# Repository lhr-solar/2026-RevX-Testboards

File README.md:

# RevX
https://www.notion.so/lhrs/Summer-2026-Rev-X-Experimental-Boards-3506309905da81d8914cc86e8693fb08?source=copy_link

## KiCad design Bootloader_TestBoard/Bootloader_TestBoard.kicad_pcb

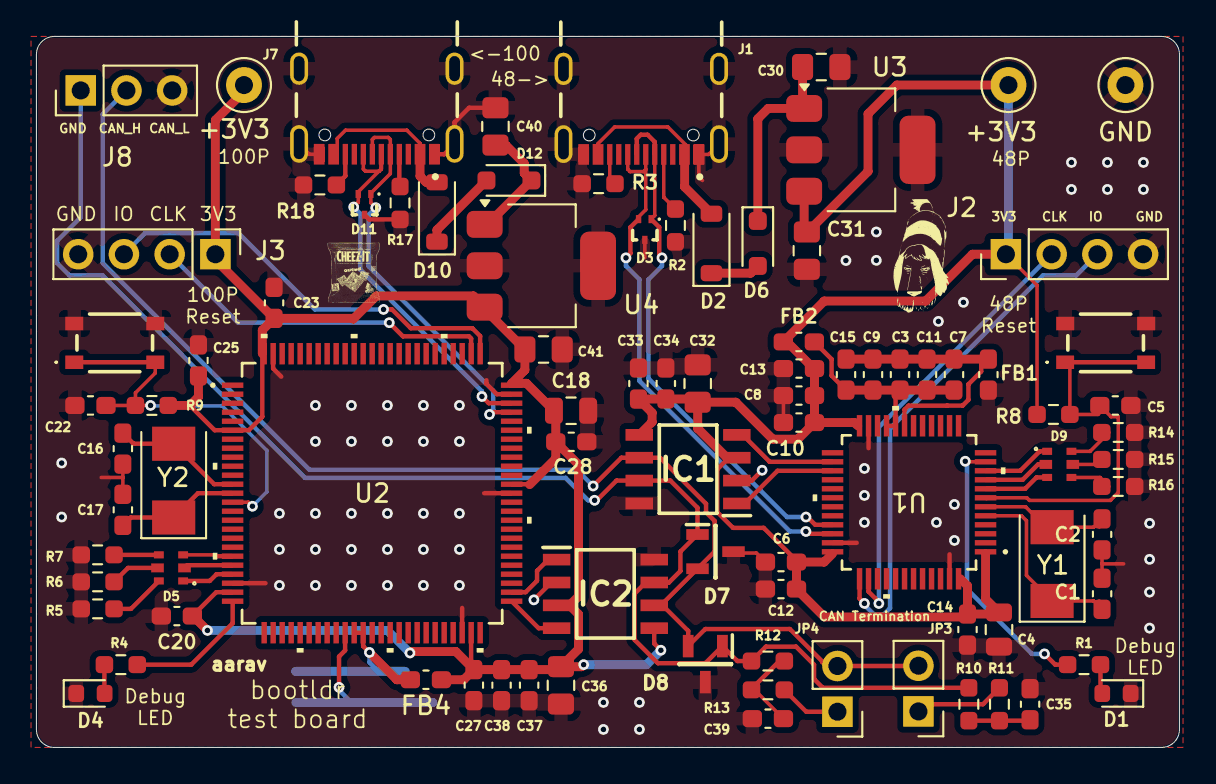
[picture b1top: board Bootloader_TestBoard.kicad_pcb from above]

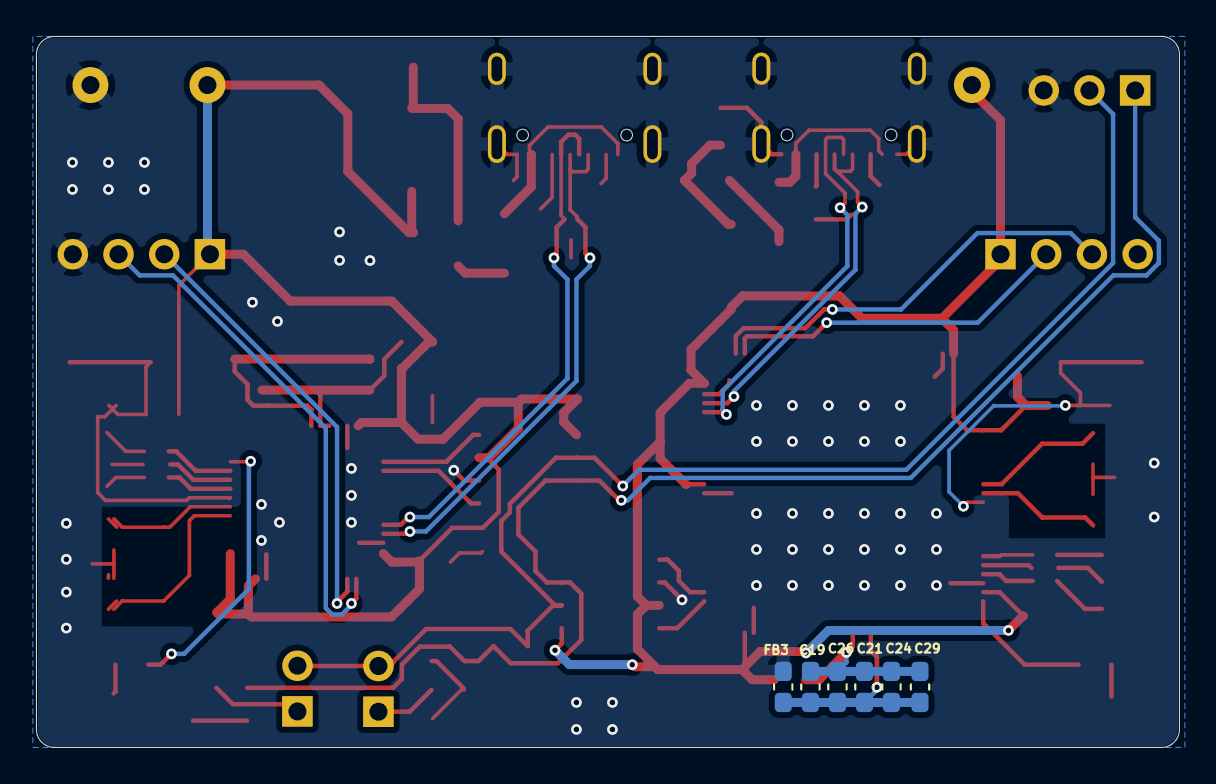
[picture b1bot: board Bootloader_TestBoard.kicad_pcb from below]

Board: 2 copper layers, 63.5 x 39.5 mm, 95 parts (6 on the bottom side), 57 nets.

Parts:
+3V3, +3V3#2: 3.3V; TestPoint_Loop_D1.80mm_Drill1.0mm_Beaded
C1, C2, C16, C17: 26p; C_0603_1608Metric_Pad1.08x0.95mm_HandSolder
C3, C5, C6, C7, C8, C10, C12, C13, C14: 0.1uF; C_0603_1608Metric_Pad1.08x0.95mm_HandSolder
C4: 10uF; C_0805_2012Metric
C9, C11: 1uF; C_0603_1608Metric_Pad1.08x0.95mm_HandSolder
C15: 100nF; C_0603_1608Metric_Pad1.08x0.95mm_HandSolder
C18: 10u; C_0805_2012Metric
C19, C20, C21, C22, C23, C25, C27, C28, C29, C33, C34, C35, C37, C38, C39: 0.1u; C_0603_1608Metric_Pad1.08x0.95mm_HandSolder
C24, C26: 1u; C_0603_1608Metric_Pad1.08x0.95mm_HandSolder
C30, C31, C32, C36, C40, C41: 10u; C_0805_2012Metric_Pad1.18x1.45mm_HandSolder
D1, D4: LED; LED_0603_1608Metric
D2, D10: D; D_SOD-123
D3, D11: TPD2EUSB30DRTR; USB_TVS
D5, D9: RGB_LED
D6, D12: SBA130CH-AU_R1_000A1; D_SOD-323_HandSoldering
D7, D8: CDSOT23-T24CAN
FB1, FB2, FB3, FB4: FerriteBead; C_0603_1608Metric_Pad1.08x0.95mm_HandSolder
GND: TestPoint; TestPoint_Loop_D1.80mm_Drill1.0mm_Beaded
IC1, IC2: TCAN3413DR
J1, J7: USB_C_Receptacle; USB_Conn
J2, J3: SWD; PinHeader_1x04_P2.54mm_Vertical
J8: Conn_01x03; PinHeader_1x03_P2.54mm_Vertical
JP3, JP4: TRM; PinHeader_1x02_P2.54mm_Vertical
R1, R4, R5, R6, R7, R14, R15, R16: 1k; R_0603_1608Metric_Pad0.98x0.95mm_HandSolder
R2, R3, R17, R18: 5.1k; R_0603_1608Metric_Pad0.98x0.95mm_HandSolder
R8, R9: 10k; R_0603_1608Metric_Pad0.98x0.95mm_HandSolder
R10, R11, R12, R13: 60; R_0603_1608Metric_Pad0.98x0.95mm_HandSolder
Reset1: Reset; TL3365AF180QG
SW1: Reset; TL3365AF180QG
U1: STM32G473CET6; 48PinMCU
U2: STM32G473VET6; 100PinMCU
U3, U4: MCP1826S; SOT-223-3_TabPin2
Y1, Y2: Crystal; Crystal_SMD_Abracon_ABM3-2Pin_5.0x3.2mm

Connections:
+3V3_48P: +3V3#2.1 (1_1), C4.1, C6.1, C8.1, C10.1, C12.1, C13.1, C14.1, C31.2, C32.1, C33.1, C34.1, FB2.1, IC1.3 (VCC), IC1.5 (SHDNV_IO), J2.1, R8.2, U1.1 (VBAT), U1.24 (VDD), U1.36 (VDD), U1.48 (VDD), U3.3 (VO)
+3V3_100P: +3V3.1 (1_1), C18.1, C20.1, C23.1, C25.1, C27.1, C28.1, C36.1, C37.1, C38.1, C41.2, FB4.1, IC2.3 (VCC), IC2.5 (SHDNV_IO), J3.1, R9.2, U2.6 (VBAT), U2.24 (VDD), U2.49 (VDD), U2.64 (VDD), U2.75 (VDD), U2.100 (VDD), U4.3 (VO)
+5V_48P: D2.1 (K), D6.2 (A)
+5V_100P: D10.1 (K), D12.2 (A)
/48Pin/GNDA: C3.2, C7.2, C9.2, C11.2, C15.2, FB1.1, U1.19 (VSSA)
/48Pin/NRST: C5.1, R8.1, SW1.1, U1.7 (PG10-NRST)
/48Pin/PA0: D9.5, U1.8 (PA0-GPIO_BLUE)
/48Pin/PA1: D9.3, U1.9 (PA1_GPIO_RED)
/48Pin/PA2: D9.1, U1.10 (PA2-GPIO_GREEN)
/48Pin/PA3: R1.1, U1.11 (PA3)
/48Pin/PB12: IC1.4 (RXD), U1.26 (PB12)
/48Pin/PB13: IC1.1 (TXD), U1.27 (PB13)
/48Pin/VDDA: C3.1, C7.1, C9.1, C11.1, C15.1, FB2.2, U1.20 (VREF+), U1.21 (VDDA)
/100Pin/GNDA: C19.2, C21.2, C24.2, C26.2, C29.2, FB3.1, U2.35 (VSSA)
/100Pin/NRST: C22.1, R9.1, Reset1.1, U2.14 (PG10-NRST)
/100Pin/PA0: D5.5, U2.20 (PA0-GPIO_BLUE)
/100Pin/PA1: D5.3, U2.21 (PA1-GPIO_RED)
/100Pin/PA2: D5.1, U2.22 (PA2-GPIO_GREEN)
/100Pin/PA3: R4.1, U2.25 (PA3)
/100Pin/PB12: IC2.4 (RXD), U2.51 (PB12)
/100Pin/PB13: IC2.1 (TXD), U2.52 (PB13)
/100Pin/VDDA: C19.1, C21.1, C24.1, C26.1, C29.1, FB4.2, U2.36 (VREF+), U2.37 (VDDA)
/CAN_H: D7.1 (CAN_H), D8.1 (CAN_H), IC1.7 (CANH), IC2.7 (CANH), J8.1, R10.1, R12.1
/CAN_L: D7.2 (CAN_L), D8.2 (CAN_L), IC1.6 (CANL), IC2.6 (CANL), J8.2, JP3.2 (B), JP4.2 (B)
/SWCLK_48P: J2.2, U1.38 (PA14)
/SWCLK_100P: J3.2, U2.77 (PA14)
/SWDIO_48P: J2.3, U1.37 (PA13)
/SWDIO_100P: J3.3, U2.76 (PA13)
/USB_DM_48P: D3.1 (D+), J1.A7 (D-), J1.B7 (D-), U1.33 (PA11)
/USB_DM_100P: D11.1 (D+), J7.A7 (D-), J7.B7 (D-), U2.72 (PA11)
/USB_DP_48P: D3.2 (D-), J1.A6 (D+), J1.B6 (D+), U1.34 (PA12)
/USB_DP_100P: D11.2 (D-), J7.A6 (D+), J7.B6 (D+), U2.73 (PA12)
GND: C1.1, C2.2, C4.2, C5.2, C6.2, C8.2, C10.2, C12.2, C13.2, C14.2, C16.1, C17.1, C18.2, C20.2, C22.2, C23.2, C25.2, C27.2, C28.2, C30.1, C31.1, C32.2, C33.2, C34.2, C35.1, C36.2, C37.2, C38.2, C39.1, C40.1, C41.1, D1.1 (K), D3.3 (GND), D4.1 (K), D7.3 (GND), D8.3 (GND), D11.3 (GND), FB1.2, FB3.2, GND.1 (1_1), IC1.2 (GND), IC1.8 (STB), IC2.2 (GND), IC2.8 (STB), J1.A1 (GND), J1.A12 (GND), J1.B1 (GND), J1.B12 (GND), J1.S1 (SHIELD), J1.S2 (Shield), J1.S3 (Shield), J1.S4 (Shield), J2.4, J3.4, J7.A1 (GND), J7.A12 (GND), J7.B1 (GND), J7.B12 (GND), J7.S1 (SHIELD), J7.S2 (Shield), J7.S3 (Shield), J7.S4 (Shield), J8.3, R2.2, R3.2, R5.2, R6.2, R7.2, R14.2, R15.2, R16.2, R17.2, R18.2, Reset1.2, SW1.2, U1.23 (VSS), U1.35 (VSS), U1.47 (VSS), U2.23 (VSS), U2.48 (VSS), U2.63 (VSS), U2.74 (VSS), U2.99 (VSS), U3.2 (GND), U4.2 (GND)
unnamed: C35.2, R10.2, R11.1
unnamed: C39.2, R12.2, R13.1
unnamed: D1.2 (A), R1.2
unnamed: D2.2 (A), J1.A4 (VBUS), J1.A9 (VBUS), J1.B4 (VBUS), J1.B9 (VBUS)
unnamed: D4.2 (A), R4.2
unnamed: D5.2, R5.1
unnamed: D5.4, R6.1
unnamed: D5.6, R7.1
unnamed: C30.2, D6.1 (K), U3.1 (VI)
unnamed: D9.2, R14.1
unnamed: D9.4, R15.1
unnamed: D9.6, R16.1
unnamed: D10.2 (A), J7.A4 (VBUS), J7.A9 (VBUS), J7.B4 (VBUS), J7.B9 (VBUS)
unnamed: C40.2, D12.1 (K), U4.1 (VI)
unnamed: J1.A5 (CC1), R2.1
unnamed: J1.B5 (CC2), R3.1
unnamed: J7.A5 (CC1), R17.1
unnamed: J7.B5 (CC2), R18.1
unnamed: JP3.1 (A), R11.2
unnamed: JP4.1 (A), R13.2
unnamed: C1.2, U1.5 (PF0-OSC_IN), Y1.1
unnamed: C2.1, U1.6 (PF1-OSC_OUT), Y1.2
unnamed: C16.2, U2.12 (PF0-OSC_IN), Y2.2
unnamed: C17.2, U2.13 (PF1-OSC_OUT), Y2.1

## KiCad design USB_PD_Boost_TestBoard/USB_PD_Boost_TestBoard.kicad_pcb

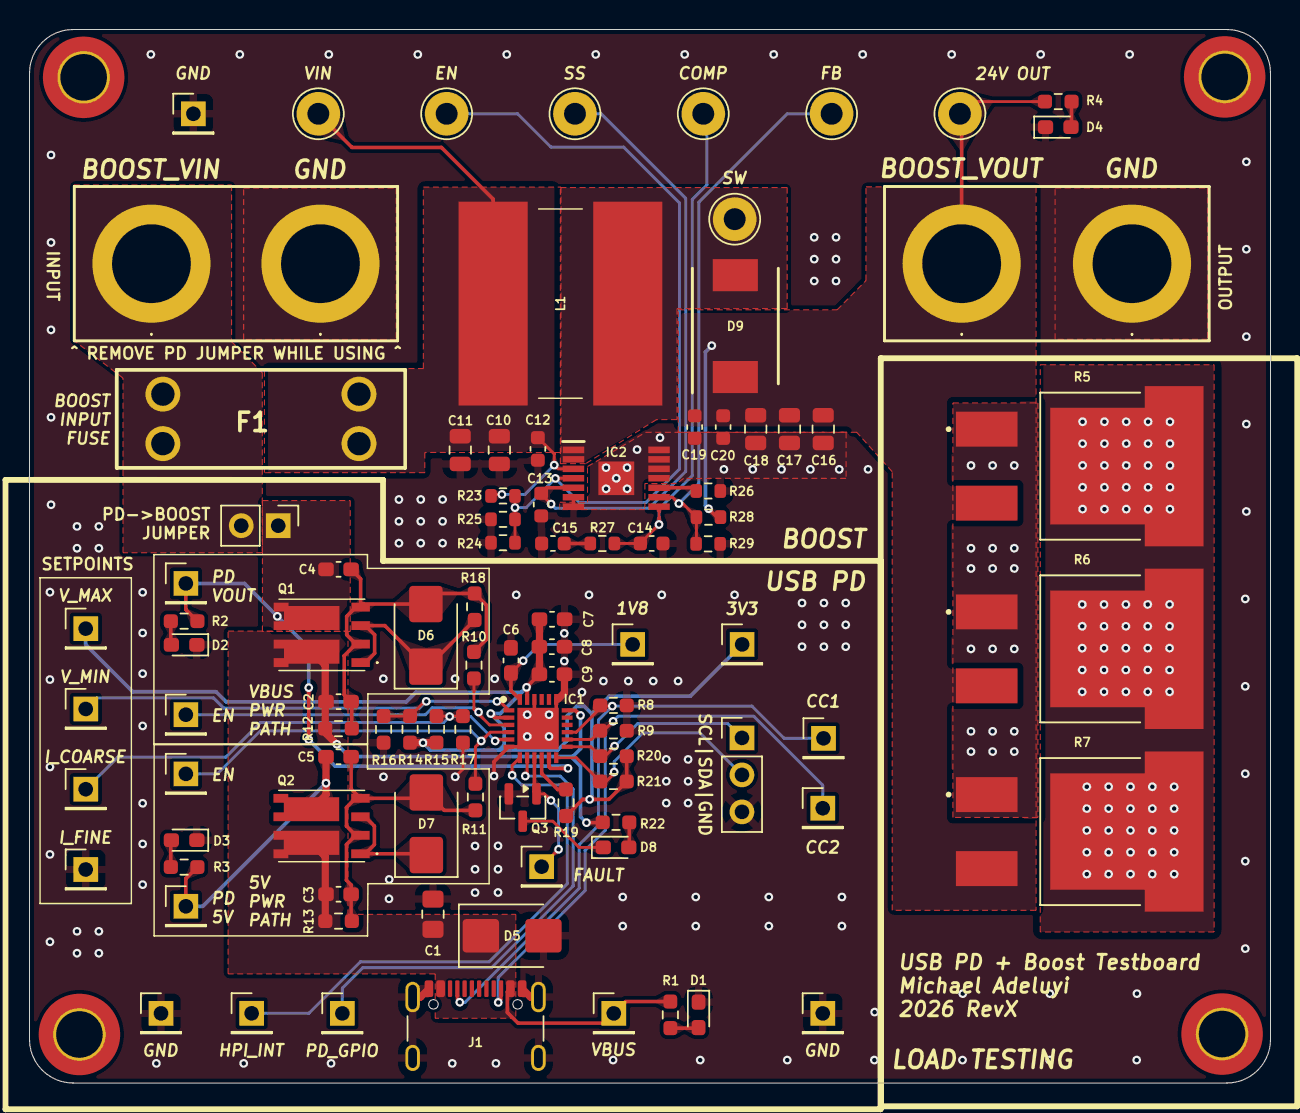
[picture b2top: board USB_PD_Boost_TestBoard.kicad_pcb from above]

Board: 2 copper layers, 85.2 x 72.4 mm, 103 parts (0 on the bottom side), 39 nets.

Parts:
C1: 10uF; C_0805_2012Metric_Pad1.18x1.45mm_HandSolder
C2, C3, C4, C5, C6, C7: 1uF; C_0603_1608Metric_Pad1.08x0.95mm_HandSolder
C8, C9: 0.1uF; C_0603_1608Metric_Pad1.08x0.95mm_HandSolder
C10, C11: 10uF; C_0805_2012Metric
C12, C15: 0.1uF; C_0603_1608Metric
C13: 0.047uF; C_0603_1608Metric
C14: 0.1nF; C_0603_1608Metric
C16, C17, C18: 4.7uF; C_0805_2012Metric
C19, C20: 1uF; C_0603_1608Metric
D1, D2: VBUS_IN; LED_0603_1608Metric_Pad1.05x0.95mm_HandSolder
D3: 5V; LED_0603_1608Metric_Pad1.05x0.95mm_HandSolder
D4: 24V; LED_0603_1608Metric_Pad1.05x0.95mm_HandSolder
D5: SMBJ24A-E3_52; D_SMB
D6, D7: SMBJ10A-E3_52; D_SMB
D8: FAULT; LED_0603_1608Metric_Pad1.05x0.95mm_HandSolder
D9: B540C-13-F
F1: 5A; Fuse-3557-2
H1, H2, H3, H4: MountingHole_3.2mm_M3_DIN965_Pad_TopBottom
IC1: CYPD3177-24LQXQ
IC2: TPS55340PWP
J1: USB_C_Receptacle_USB2.0_16P; USB_C_Receptacle_GCT_USB4105-xx-A_16P_TopMnt_Horizontal
J2: PD_12C; PinHeader_1x03_P2.54mm_Vertical
J3, J4, J5, J6: 575-4; 5754
JP1: BoostJumper; PinHeader_1x02_P2.54mm_Vertical
L1: 10uH; SDR1307-100ML
LOGO1: LHRS; LHRs_LOGO
Q1, Q2: SI7997DP-T1-GE3
Q3: IRLML0030; SOT-23
R1, R2, R22: 3.3k; R_0603_1608Metric_Pad0.98x0.95mm_HandSolder
R3, R10, R11, R16: 1k; R_0603_1608Metric_Pad0.98x0.95mm_HandSolder
R4: 4.3k; R_0603_1608Metric_Pad0.98x0.95mm_HandSolder
R5, R6, R7: 33; RES_PWR263S-35
R8, R9, R14, R15, R17: 5.1k; R_0603_1608Metric_Pad0.98x0.95mm_HandSolder
R12: 10k; R_0603_1608Metric_Pad0.98x0.95mm_HandSolder
R13, R18: 49.9k; R_0603_1608Metric_Pad0.98x0.95mm_HandSolder
R19: 4.7k; R_0603_1608Metric_Pad0.98x0.95mm_HandSolder
R20, R21: 2.2k; R_0603_1608Metric_Pad0.98x0.95mm_HandSolder
R23: 301k; R_0603_1608Metric
R24: 51.1k; R_0603_1608Metric
R25: 0; R_0603_1608Metric
R26: 78.7k; R_0603_1608Metric
R27: 2.21k; R_0603_1608Metric
R28: 187k; R_0603_1608Metric
R29: 10k; R_0603_1608Metric
TP1, TP2, TP3: GND; PinHeader_1x01_P2.54mm_Vertical
TP4: CC2; PinHeader_1x01_P2.54mm_Vertical
TP5: CC1; PinHeader_1x01_P2.54mm_Vertical
TP6: SAFE_PWR_EN; PinHeader_1x01_P2.54mm_Vertical
TP7: VBUS_FET_EN; PinHeader_1x01_P2.54mm_Vertical
TP8: VBUS_MAX; PinHeader_1x01_P2.54mm_Vertical
TP9: VBUS_MIN; PinHeader_1x01_P2.54mm_Vertical
TP10: ISINK_COARSE; PinHeader_1x01_P2.54mm_Vertical
TP11: ISINK_FINE; PinHeader_1x01_P2.54mm_Vertical
TP12: PD_GPIO_1; PinHeader_1x01_P2.54mm_Vertical
TP13: PD_HPI_INT; PinHeader_1x01_P2.54mm_Vertical
TP14: VBUS_IN; PinHeader_1x01_P2.54mm_Vertical
TP15: PD_VBUS_OUT; PinHeader_1x01_P2.54mm_Vertical
TP16: PD_5V_OUT; PinHeader_1x01_P2.54mm_Vertical
TP17: PD_1V8; PinHeader_1x01_P2.54mm_Vertical
TP18: PD_3V3; PinHeader_1x01_P2.54mm_Vertical
TP19: PD_FAULT; PinHeader_1x01_P2.54mm_Vertical
TP20: Vin; TestPoint_THTPad_D3.0mm_Drill1.5mm
TP21: EN; TestPoint_THTPad_D3.0mm_Drill1.5mm
TP22: SS; TestPoint_THTPad_D3.0mm_Drill1.5mm
TP23: COMP; TestPoint_THTPad_D3.0mm_Drill1.5mm
TP24: SW; TestPoint_THTPad_D3.0mm_Drill1.5mm
TP25: FB; TestPoint_THTPad_D3.0mm_Drill1.5mm
TP26: Vout; TestPoint_THTPad_D3.0mm_Drill1.5mm

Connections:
/BOOST_24V_OUT: C16.1, C17.1, C18.1, C19.1, C20.1, D9.1 (K), J5.1, R4.1, R5.2, R6.2, R7.2, R28.1, TP26.1
/BOOST_VIN: F1.1, J3.1, JP1.2 (B)
/CC1: IC1.15 (CC1), J1.A5 (CC1), R8.1, TP5.1
/CC2: IC1.14 (CC2), J1.B5 (CC2), R9.1, TP4.1
/DISSIPATION: R5.3, R6.3, R7.3
/PD_5V_OUT: C5.1, Q2.5 (D2), Q2.6 (D2), Q2.10 (D2), Q2.12 (D2), R3.1, TP16.1
/PD_VOUT: C4.1, IC1.11 (VDC_OUT), JP1.1 (A), Q1.5 (D2), Q1.6 (D2), Q1.10 (D2), Q1.12 (D2), R2.1, TP15.1
/USB_PD/ISINK_COARSE: IC1.5 (ISNK_COARSE), R15.2, R17.1, TP10.1
/USB_PD/PD_1V8: C6.2, IC1.24 (VCCD), TP17.1
/USB_PD/PD_3V3: C7.1, C8.1, C9.1, IC1.2 (VBUS_MAX), IC1.23 (VDDD), R14.1, R15.1, R19.1, R20.1, R21.1, TP8.1, TP18.1
/USB_PD/PD_FAULT: IC1.9 (FAULT), Q3.1 (G), TP19.1
/USB_PD/PD_GPIO_1: IC1.8 (GPIO_1), TP12.1
/USB_PD/PD_HPI_INT: IC1.7 (HPI_INT), TP13.1
/USB_PD/PD_SCL: IC1.13 (HPI_SCL), J2.1, R20.2
/USB_PD/PD_SDA: IC1.12 (HPI_SDA), J2.2, R21.2
/USB_PD/SAFE_PWR_EN: IC1.4 (SAFE_PWR_EN), R11.2, TP6.1
/USB_PD/VBUS_FET_EN: IC1.3 (VBUS_FET_EN), R10.2, TP7.1
/USB_PD/VBUS_MIN: IC1.1 (VBUS_MIN), R14.2, R16.1, TP9.1
/USB_PD_Boost/+USB_PD: C10.1, C11.1, C12.1, F1.2, IC2.3 (VIN), L1.1, R23.1, TP20.1
/VBUS_IN: C1.1, C2.1, C3.1, D5.1 (K), IC1.18 (VBUS_IN), J1.A4 (VBUS), J1.A9 (VBUS), J1.B4 (VBUS), J1.B9 (VBUS), Q1.7 (D1), Q1.8 (D1), Q1.9 (D1), Q1.11 (D1), Q2.7 (D1), Q2.8 (D1), Q2.9 (D1), Q2.11 (D1), R1.1, R12.2, R13.2, R22.1, TP14.1
GND: C1.2, C6.1, C7.2, C8.2, C9.2, C10.2, C11.2, C12.2, C13.2, C14.2, C15.2, C16.2, C17.2, C18.2, C19.2, C20.2, D1.1 (K), D2.1 (K), D3.1 (K), D4.1 (K), D5.2 (A), IC1.6 (ISNK_FINE), IC1.19 (GND_1), IC1.22 (GND_2), IC1.25 (GND_3), IC2.6 (SYNC), IC2.7 (AGND), IC2.11 (NC), IC2.12 (PGND_1), IC2.13 (PGND_2), IC2.14 (PGND_3), IC2.15 (EP), J1.A1 (GND), J1.A12 (GND), J1.B1 (GND), J1.B12 (GND), J1.S1 (SHIELD), J1.S2 (Shield), J1.S3 (Shield), J1.S4 (Shield), J2.3, J4.1, J6.1, Q3.2 (S), R5.1, R6.1, R7.1, R8.2, R9.2, R16.2, R17.2, R24.2, R25.1, R26.2, R29.2, TP1.1, TP2.1, TP3.1, TP11.1
unnamed: C15.1, R27.2
unnamed: D1.2 (A), R1.2
unnamed: D2.2 (A), R2.2
unnamed: D3.2 (A), R3.2
unnamed: D4.2 (A), R4.2
unnamed: C2.2, C4.2, D6.2 (A), Q1.2 (G1), Q1.4 (G2), R10.1, R12.1, R18.1
unnamed: D6.1 (K), Q1.1 (S1), Q1.3 (S2), R18.2
unnamed: C3.2, C5.2, D7.2 (A), Q2.2 (G1), Q2.4 (G2), R11.1, R13.1
unnamed: D7.1 (K), Q2.1 (S1), Q2.3 (S2)
unnamed: D8.2 (A), R22.2
unnamed: D8.1 (K), Q3.3 (D)
unnamed: D9.2 (A), IC2.1 (SW_1), IC2.2 (SW_2), L1.2, TP24.1
unnamed: IC1.10 (FLIP), R19.2
unnamed: C14.1, IC2.8 (COMP), R27.1, TP23.1
unnamed: IC2.4 (EN), R23.2, R24.1, R25.2, TP21.1
unnamed: IC2.9 (FB), R28.2, R29.1, TP25.1
unnamed: IC2.10 (FREQ), R26.1
unnamed: C13.1, IC2.5 (SS), TP22.1

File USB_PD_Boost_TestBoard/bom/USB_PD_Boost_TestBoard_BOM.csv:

Reference,Qty,Value,LCSC P/N,P/N
Q3,1,IRLML0030,C67272,IRLML0030TRPBF
D8,1,FAULT,C84263,NCD0603R1
"D1,D2",2,VBUS_IN,C7371904,XL-1608UBC-06A
D3,1,5V,C7371904,XL-1608UBC-06A
D4,1,24V,C7371904,XL-1608UBC-06A
"R5,R6,R7",3,33,C1356479,PWR263S-35-33R0F
J1,1,USB_C_Receptacle_USB2.0_16P,C393939,USB4105-GF-A
F1,1,5A,C3205238,3557-2
D9,1,B540C-13-F,C72264,B540C-13-F
IC1,1,CYPD3177-24LQXQ,C2959321,CYPD3177-24LQXQ
L1,1,10uH,C49672242,SDR1307-100ML
"Q1,Q2",2,SI7997DP-T1-GE3,C913432,SI7997DP-T1-GE3
D5,1,SMBJ24A-E3_52,C435936,SMBJ24A-E3/52
"D6,D7",2,SMBJ10A-E3_52,C1973203,SMBJ10A-E3/52
IC2,1,TPS55340PWP,C43862,TPS55340PWP
C1,1,10uF,C440198,GRM21BR61H106KE43K
"C2,C3,C4,C5,C6,C7",6,1uF,C15849,MLASU168SB5105KTNA01
"C8,C9",2,0.1uF,C14663,MLASH168SB7104KTNA01
"C10,C11",2,10uF,C3840574,GRM21BR61H106KE43K
"C12,C15",2,0.1uF,C6666325,MLASH168SB7104KTNA01
C13,1,0.047uF,C107093,CC0603KRX7R9BB473
C14,1,0.1nF,C14665,CC0603JRNPO9BN101
"C16,C17,C18",3,4.7uF,C6962403,08055D475KAT4A
"C19,C20",2,1uF,C559769,CC0603KRX7R9BB105
"J3,J4,J5,J6",4,575-4,C4944061,575-4 
"R1,R2,R22",3,3.3k,C2907023,CRCW06033K30FKTA
"R3,R10,R11,R16",4,1k,C21190,CRCW06031K00FKEI 
R4,1,4.3k,C2907165,CRCW06034K30FKEA
"R8,R9,R14,R15,R17",5,5.1k,C23186,CRCW06035K10FKEC 
R12,1,10k,C25804,CRCW060310K0FKEI 
"R13,R18",2,49.9k,C4117233,CRCW060349K9FKEC
R19,1,4.7k,C23162,CRCW06034K70FKEA
"R20,R21",2,2.2k,C844925,CRCW06032K20FKEA
R23,1,301k,C273742,RC0603FR-07301KL
R24,1,51.1k,C844575,CRCW060351K1FKEA
R26,1,78.7k,C3961380,RC0603DR-0778K7L
R27,1,2.21k,C705758,RT0603BRD072K21L
R28,1,187k,C2085290,CRCW0603187KFKEA
R29,1,10k,C843841,CRCW060310K0FKEI

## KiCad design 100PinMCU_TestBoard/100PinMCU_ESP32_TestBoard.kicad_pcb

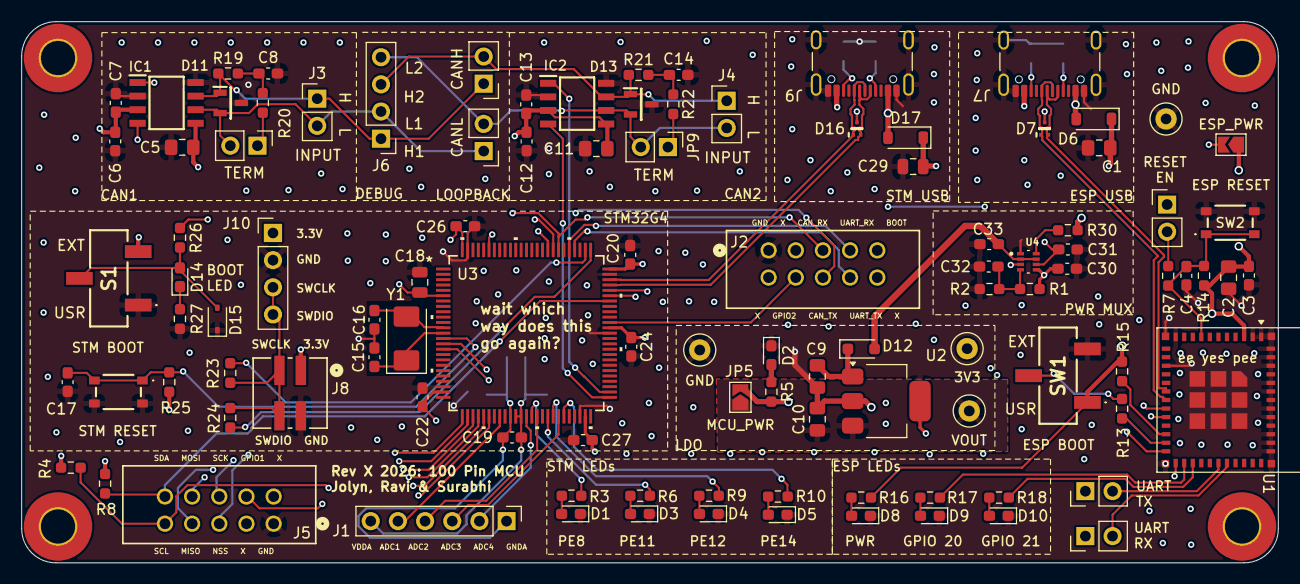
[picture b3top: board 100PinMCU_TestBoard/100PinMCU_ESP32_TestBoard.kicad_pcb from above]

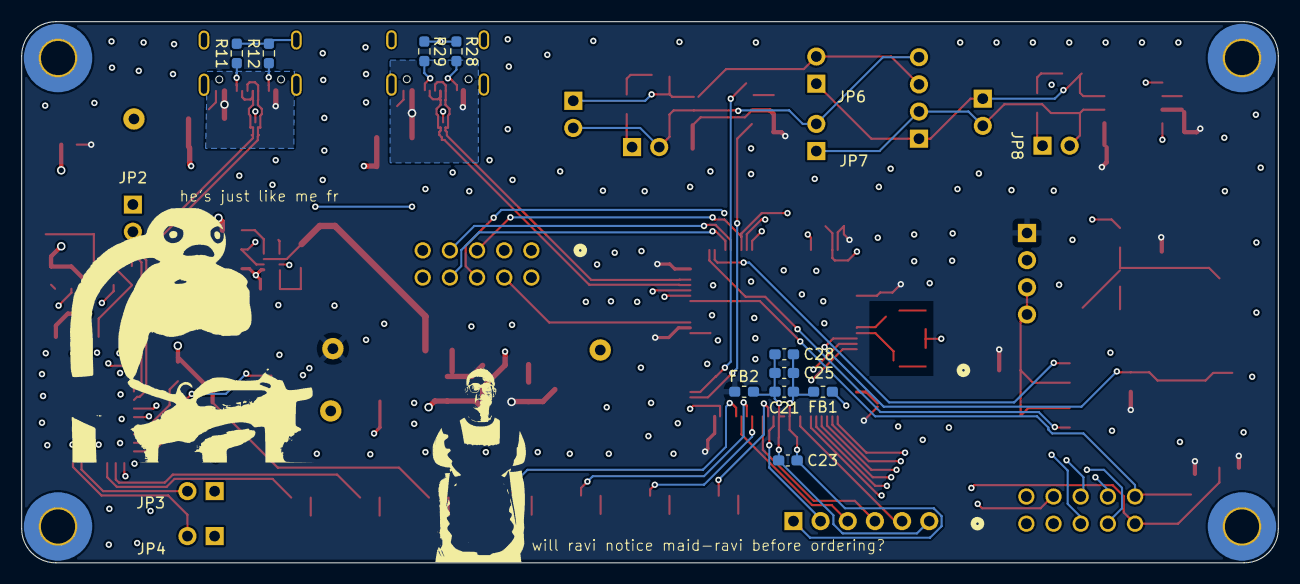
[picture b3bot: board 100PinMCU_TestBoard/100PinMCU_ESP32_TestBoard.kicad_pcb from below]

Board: 4 copper layers, 117.5 x 50.6 mm, 120 parts (10 on the bottom side), 83 nets.

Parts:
C1, C2: 10uF; C_0805_2012Metric_Pad1.18x1.45mm_HandSolder
C3, C4, C17, C19, C20, C21, C22, C24, C26, C27, C28, C30, C31, C32, C33: 0.1uF; C_0603_1608Metric_Pad1.08x0.95mm_HandSolder
C5, C9, C10, C11: 10u; C_0805_2012Metric_Pad1.18x1.45mm_HandSolder
C6, C7, C8, C12, C13, C14: 0.1u; C_0603_1608Metric_Pad1.08x0.95mm_HandSolder
C15, C16: 26p; C_0603_1608Metric_Pad1.08x0.95mm_HandSolder
C18, C29: 10uF; C_0805_2012Metric
C23, C25: 1uF; C_0603_1608Metric_Pad1.08x0.95mm_HandSolder
D1, D3, D4, D5, D14: LED; D_0603_1608Metric_Pad1.05x0.95mm_HandSolder
D2: 3V3; D_0603_1608Metric_Pad1.05x0.95mm_HandSolder
D6, D17: D_Schottky; D_SOD-123
D7, D16: TPD2EUSB30DRTR
D8: ESP_PWR; D_0603_1608Metric_Pad1.05x0.95mm_HandSolder
D9: ESP_LED1; D_0603_1608Metric_Pad1.05x0.95mm_HandSolder
D10: ESP_LED2; D_0603_1608Metric_Pad1.05x0.95mm_HandSolder
D11, D13: CDSOT23-T24CAN
D12: SBA130CH-AU_R1_000A1; D_SOD-323_HandSoldering
D15: D_TVS; D_SOD-323
FB1, FB2: FerriteBead; L_0603_1608Metric_Pad1.05x0.95mm_HandSolder
H1, H2, H3, H4: MountingHole_Pad; MountingHole_3.2mm_M3_Pad_TopBottom
IC1, IC2: TCAN3413DR
J1: ADC_Breakout; PinHeader_1x06_P2.54mm_Vertical
J2: LogicAnalyzer_1; CONN_SFH11-xxxC-D05-ST-XX_SUL
J3: CAN_1; PinHeader_1x02_P2.54mm_Vertical
J4: CAN_2; PinHeader_1x02_P2.54mm_Vertical
J5: LogicAnalyzer_2; CONN_SFH11-xxxC-D05-ST-XX_SUL
J6: CAN_Breakout; PinHeader_1x04_P2.54mm_Vertical
J7, J9: USB_C_Receptacle_USB2.0_16P; USB_C_Receptacle_GCT_USB4105-xx-A_16P_TopMnt_Horizontal
J8: SWD_Header_02x02; CONN04_878320406_MOL
J10: SWD_PinHeader; PinHeader_1x04_P2.54mm_Vertical
JP1: ESP_PWR; SolderJumper-2_P1.3mm_Open_TrianglePad1.0x1.5mm
JP2: ESP_RST_EN; PinHeader_1x02_P2.54mm_Vertical
JP3: ESP_TX_EN; PinHeader_1x02_P2.54mm_Vertical
JP4: ESP_RX_EN; PinHeader_1x02_P2.54mm_Vertical
JP5: MCU_PWR; SolderJumper-2_P1.3mm_Open_TrianglePad1.0x1.5mm
JP6: CAN_H_LOOPBACK; PinHeader_1x02_P2.54mm_Vertical
JP7: CAN_L_LOOPBACK; PinHeader_1x02_P2.54mm_Vertical
JP8, JP9: TRM; PinHeader_1x02_P2.54mm_Vertical
R1: 16k; R_0603_1608Metric_Pad0.98x0.95mm_HandSolder
R2, R4, R8: 4.7k; R_0603_1608Metric_Pad0.98x0.95mm_HandSolder
R3, R5, R6, R7, R9, R10, R16, R17, R18, R27: 1k; R_0603_1608Metric_Pad0.98x0.95mm_HandSolder
R11, R12, R28, R29: 5.1k; R_0603_1608Metric_Pad0.98x0.95mm_HandSolder
R13, R14, R15, R25, R26, R30: 10k; R_0603_1608Metric_Pad0.98x0.95mm_HandSolder
R19, R20, R21, R22: 60; R_0603_1608Metric_Pad0.98x0.95mm_HandSolder
R23, R24: 22; R_0603_1608Metric_Pad0.98x0.95mm_HandSolder
Reset1: Reset; TL3365AF180QG
S1: 450406020024
SW1: BOOT Switch; 450406020024
SW2: RESET Button; TL3365AF180QG
TP1, TP3: GND; TestPoint_Loop_D1.80mm_Drill1.0mm_Beaded
TP2: 3V3; TestPoint_Loop_D1.80mm_Drill1.0mm_Beaded
TP_3.3V1: 3.3V; TestPoint_Loop_D1.80mm_Drill1.0mm_Beaded
U1: ESP32-C6-MINI-1
U2: MCP1826S; SOT-223-3_TabPin2
U3: STM32G491VET6; LQFP_491VET6_STM
U4: TPS2117DRLR
Y1: Crystal; Crystal_SMD_Abracon_ABM3-2Pin_5.0x3.2mm

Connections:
+3.3V: C5.1, C6.1, C7.1, C11.1, C12.1, C13.1, C18.1, C20.1, C22.1, C24.1, C26.1, C27.1, FB2.1, IC1.3 (VCC), IC1.5 (SHDNV_IO), IC2.3 (VCC), IC2.5 (SHDNV_IO), J8.1, J10.1, JP1.2 (B), JP5.2 (B), R4.1, R5.1, R8.1, R25.2, S1.3 (C), TP2.1, U3.6 (VBAT), U3.24 (VDD), U3.49 (VDD), U3.64 (VDD), U3.75 (VDD), U3.100 (VDD)
+3.3V_ESP: C2.1, C3.1, JP1.1 (A), R14.1, R15.2, R16.1, SW1.1 (A), U1.3 (3V3)
/100PinMCU/GNDA: C19.2, C21.2, C23.2, C25.2, C28.2, FB1.2, J1.1, U3.35 (VSSA)
/100PinMCU/PA9: JP3.1 (A), U3.70 (PA9)
/100PinMCU/PA10: JP4.1 (A), U3.71 (PA10)
/100PinMCU/PC0: U1.24 (GPIO18), U3.15 (PC0)
/100PinMCU/PC1: U1.25 (GPIO19), U3.16 (PC1)
/100PinMCU/PD2: JP2.1 (A), U3.84 (PD2)
/100PinMCU/PE8: R3.1, U3.39 (PE8)
/100PinMCU/PE11: R6.1, U3.42 (PE11)
/100PinMCU/PE12: R9.1, U3.43 (PE12)
/100PinMCU/PE14: R10.1, U3.45 (PE14)
/100PinMCU/PG10-NRST: C17.1, R25.1, Reset1.1, U1.19 (GPIO14), U3.14 (PG10-NRST)
/100PinMCU/SWCLK: R23.1, U3.77 (PA14)
/100PinMCU/SWDIO: R24.1, U3.76 (PA13)
/100PinMCU/VDDA: C19.1, C21.1, C23.1, C25.1, C28.1, FB2.2, J1.6, U3.36 (VREF+), U3.37 (VDDA)
/ADC3_IN1: J1.5, U3.33 (PB1)
/ADC3_IN2: J1.4, U3.40 (PE9)
/ADC3_IN3: J1.3, U3.44 (PE13)
/ADC3_IN4: J1.2, U3.38 (PE7)
/BOOT: J2.9 (CH1), R26.1, U1.20 (GPIO15), U3.95 (PB8-BOOT0)
/CAN_H1: D11.1 (CAN_H), IC1.7 (CANH), J3.1, J6.1, JP6.1 (A), R19.1
/CAN_H2: D13.1 (CAN_H), IC2.7 (CANH), J4.1, J6.3, JP6.2 (B), R21.1
/CAN_L1: D11.2 (CAN_L), IC1.6 (CANL), J3.2, J6.2, JP7.1 (A), JP8.2 (B)
/CAN_L2: D13.2 (CAN_L), IC2.6 (CANL), J4.2, J6.4, JP7.2 (B), JP9.2 (B)
/D+: D16.1 (D+), J9.A6 (D+), J9.B6 (D+), U3.73 (PA12)
/D-: D16.2 (D-), J9.A7 (D-), J9.B7 (D-), U3.72 (PA11)
/ESP32/+5V_LDO_IN: C1.1, C30.1, D6.1 (K), R1.1, R30.1, U4.3 (VIN1), U4.5 (MODE)
/ESP32/BOOT: R13.1, U1.23 (GPIO9)
/ESP32/ESP_RESET: C4.1, R7.2, R14.2, SW2.1, U1.8 (EN/CHIP_PU)
/ESP32/ESP_UART_RX: JP4.2 (B), U1.31 (U0TXD/GPIO16)
/ESP32/ESP_UART_TX: JP3.2 (B), U1.30 (U0RXD/GPIO17)
/ESP32/LED1: R17.1, U1.26 (GPIO20)
/ESP32/LED2: R18.1, U1.27 (GPIO21)
/ESP32/USB_D+: D7.1 (D+), J7.A6 (D+), J7.B6 (D+), U1.18 (GPIO13/USB_D+)
/ESP32/USB_D-: D7.2 (D-), J7.A7 (D-), J7.B7 (D-), U1.17 (GPIO12/USB_D-)
/ESP32/VBUSB: D6.2 (A), J7.A4 (VBUS), J7.A9 (VBUS), J7.B4 (VBUS), J7.B9 (VBUS)
/FDCAN1_RX: IC1.4 (RXD), J2.5 (CH5), U3.82 (PD0)
/FDCAN1_TX: IC1.1 (TXD), J2.6 (CH4), U3.83 (PD1)
/FDCAN2_RX: IC2.4 (RXD), U3.51 (PB12)
/FDCAN2_TX: IC2.1 (TXD), U3.52 (PB13)
/GPIO1: J5.4 (CH6), U3.31 (PC5)
/GPIO2: J2.4 (CH6), U3.65 (PC6)
/I2C2_SCL: J5.9 (CH1), R4.2, U3.30 (PC4)
/I2C2_SDA: J5.10 (CH0), R8.2, U3.69 (PA8)
/LDO/Vin: C33.1, D12.2 (A), U4.2 (VOUT), U4.7 (VOUT__1)
/LDO/Vout: C10.2, JP5.1 (A), TP_3.3V1.1, U2.3 (VO)
/Power_Mux/PR1: C32.1, R1.2, R2.1, U4.4 (PR1)
/Power_Mux/VIN_2: C29.2, C31.1, D17.1 (K), U4.6 (VIN2)
/SPI1_MISO: J5.7 (CH3), U3.28 (PA6)
/SPI1_MOSI: J5.8 (CH2), U3.29 (PA7)
/SPI1_NSS: J5.5 (CH5), U3.26 (PA4)
/SPI1_SCK: J5.6 (CH4), U3.27 (PA5)
/UART_RX: J2.7 (CH3), U3.80 (PC11)
/UART_TX: J2.8 (CH2), U3.79 (PC10)
/USB-C/CC1: J9.A5 (CC1), R29.2
/USB-C/CC2: J9.B5 (CC2), R28.2
/USB-C/VBUS_IN: D17.2 (A), J9.A4 (VBUS), J9.A9 (VBUS), J9.B4 (VBUS), J9.B9 (VBUS)
GND: C1.2, C2.2, C3.2, C4.2, C5.2, C6.2, C7.2, C8.1, C9.1, C10.1, C11.2, C12.2, C13.2, C14.1, C15.1, C16.1, C17.2, C18.2, C20.2, C22.2, C24.2, C26.2, C27.2, C29.1, C30.2, C31.2, C32.2, C33.2, D1.1 (K), D2.1 (K), D3.1 (K), D4.1 (K), D5.1 (K), D7.3 (GND), D8.1 (K), D9.1 (K), D10.1 (K), D11.3 (GND), D13.3 (GND), D15.1 (A1), D16.3 (GND), FB1.1, IC1.2 (GND), IC1.8 (STB), IC2.2 (GND), IC2.8 (STB), J2.1 (GND), J5.1 (GND), J7.A1 (GND), J7.A12 (GND), J7.B1 (GND), J7.B12 (GND), J7.S1 (SHIELD), J7.S2 (Shield), J7.S3 (Shield), J7.S4 (Shield), J8.2, J9.A1 (GND), J9.A12 (GND), J9.B1 (GND), J9.B12 (GND), J9.S1 (SHIELD), J9.S2 (Shield), J9.S3 (Shield), J9.S4 (Shield), J10.2, R2.2, R11.2, R12.2, R27.2, R28.1, R29.1, Reset1.2, S1.1 (A), SW1.3 (C), SW2.2, TP1.1, TP3.1, U1.1 (GND), U1.2 (GND), U1.11 (GND), U1.14 (GND), U1.36 (GND), U1.37 (GND), U1.38 (GND), U1.39 (GND), U1.40 (GND), U1.41 (GND), U1.42 (GND), U1.43 (GND), U1.44 (GND), U1.45 (GND), U1.46 (GND), U1.47 (GND), U1.48 (GND), U1.49 (GND), U1.50 (GND), U1.51 (GND), U1.52 (GND), U1.53 (GND), U2.2 (GND), U3.23 (VSS), U3.48 (VSS), U3.63 (VSS), U3.74 (VSS), U3.99 (VSS), U4.1 (GND)
unnamed: C8.2, R19.2, R20.1
unnamed: C14.2, R21.2, R22.1
unnamed: D1.2 (A), R3.2
unnamed: D2.2 (A), R5.2
unnamed: D3.2 (A), R6.2
unnamed: D4.2 (A), R9.2
unnamed: D5.2 (A), R10.2
unnamed: D8.2 (A), R16.2
unnamed: D9.2 (A), R17.2
unnamed: D10.2 (A), R18.2
unnamed: C9.2, D12.1 (K), U2.1 (VI)
unnamed: D14.2 (A), D15.2 (A2), R26.2, S1.2 (B)
unnamed: D14.1 (K), R27.1
unnamed: J7.A5 (CC1), R11.1
unnamed: J7.B5 (CC2), R12.1
unnamed: J8.3, J8.4, J10.3, J10.4, R23.2, R24.2
unnamed: JP2.2 (B), R7.1
unnamed: JP8.1 (A), R20.2
unnamed: JP9.1 (A), R22.2
unnamed: R13.2, SW1.2 (B)
unnamed: R15.1, U1.22 (GPIO8)
unnamed: C16.2, U3.12 (PF0-OSC_IN), Y1.2
unnamed: C15.2, U3.13 (PF1-OSC_OUT), Y1.1
unnamed: R30.2, U4.8 (ST)

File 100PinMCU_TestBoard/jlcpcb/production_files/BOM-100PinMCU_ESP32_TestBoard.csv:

Comment,Designator,Footprint,LCSC,Quantity
MCP1826S,U2,SOT-223-3_TabPin2,C126055,1
Crystal,Y1,Crystal_SMD_Abracon_ABM3-2Pin_5.0x3.2mm,C144380,1
0.1u,"C12,C13,C14,C17,C19,C20,C21,C22,C24,C26,C27,C28,C3,C4,C6,C7,C8",C_0603_1608Metric_Pad1.08x0.95mm_HandSolder,C14663,17
1uF,"C23,C25",C_0603_1608Metric_Pad1.08x0.95mm_HandSolder,C15849,2
60,"R19,R20,R21,R22",R_0603_1608Metric_Pad0.98x0.95mm_HandSolder,C166918,4
SWD_Header_02x02,J8,CONN04_878320406_MOL,C17492485,1
SBA130CH-AU_R1_000A1,D12,D_SOD-323_HandSoldering,C191023,1
1k,"R10,R16,R17,R18,R27,R3,R5,R6,R7,R9",R_0603_1608Metric_Pad0.98x0.95mm_HandSolder,C21190,10
TCAN3413DR,"IC1,IC2",TCAN3413DR,C22433320,2
4.7k,"R4,R8",R_0603_1608Metric_Pad0.98x0.95mm_HandSolder,C23162,2
5.1k,"R11,R12,R28,R29",R_0603_1608Metric_Pad0.98x0.95mm_HandSolder,C23186,4
10k,"R13,R14,R15,R25,R26",R_0603_1608Metric_Pad0.98x0.95mm_HandSolder,C25804,5
FerriteBead,"FB1,FB2",L_0603_1608Metric_Pad1.05x0.95mm_HandSolder,C2649096,2
Reset,"Reset1,SW2",TL3365AF180QG,C2886926,2
22,"R23,R24",R_0603_1608Metric_Pad0.98x0.95mm_HandSolder,C2930077,2
CDSOT23-T24CAN,"D11,D13",CDSOT23-T24CAN,C2959841,2
USB_C_Receptacle_USB2.0_16P,J7,USB_C_Receptacle_GCT_USB4105-xx-A_16P_TopMnt_Horizontal,C3020560,1
STM32G491VET6,U3,LQFP_491VET6_STM,C3209873,1
10uF,"C1,C10,C11,C18,C2,C29,C5,C9",C_0805_2012Metric_Pad1.18x1.45mm_HandSolder,C440198,8
ESP32-C6-MINI-1,U1,ESP32-C6-MINI-1,C5736265,1
D_TVS,D15,D_SOD-323,C725495,1
LED,"D1,D10,D14,D2,D3,D4,D5,D8,D9",D_0603_1608Metric_Pad1.05x0.95mm_HandSolder,C7371904,9
D_Schottky,"D17,D6",D_SOD-123,C82544,2
26p,"C15,C16",C_0603_1608Metric_Pad1.08x0.95mm_HandSolder,C92670,2
TPD2EUSB30DRTR,"D16,D7",TPD2EUSB30DRTR,C97502,2

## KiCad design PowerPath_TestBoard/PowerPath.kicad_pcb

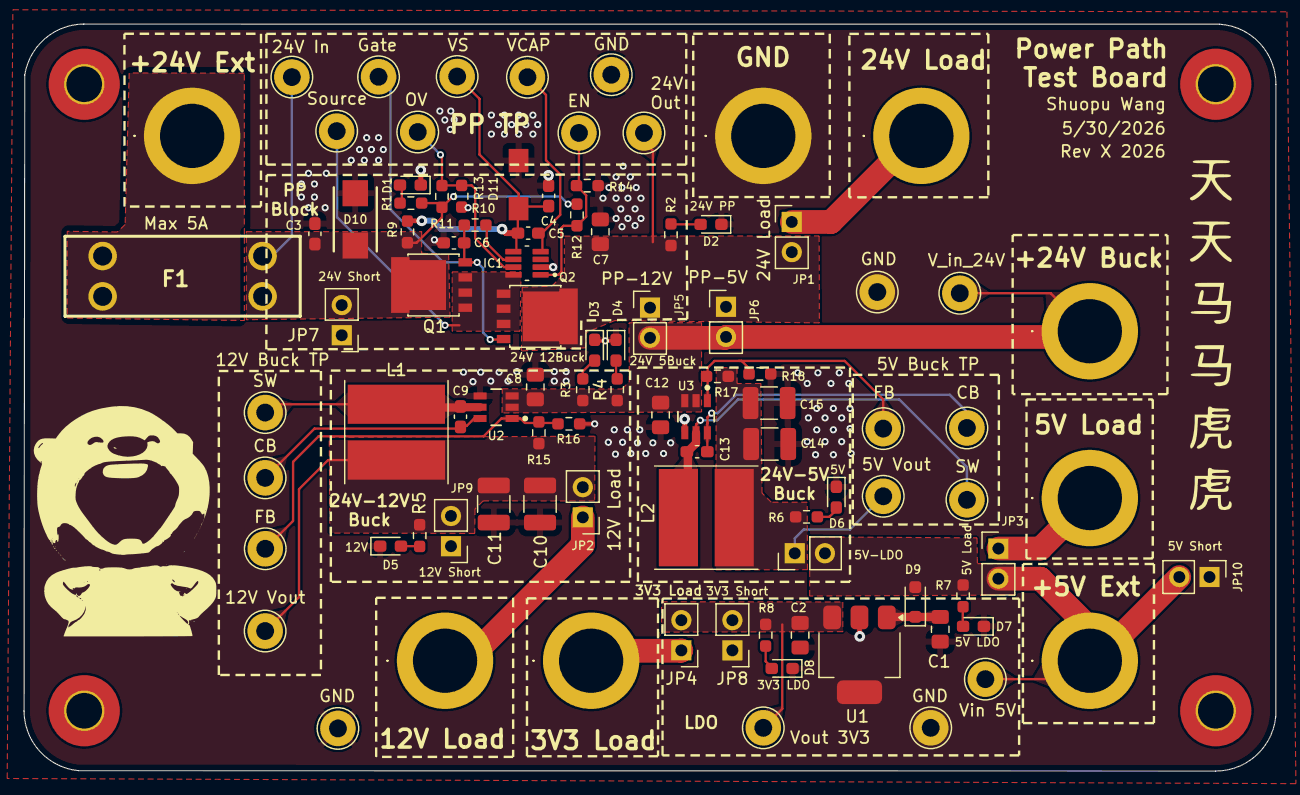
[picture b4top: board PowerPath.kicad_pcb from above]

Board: 2 copper layers, 105.4 x 62.9 mm, 99 parts (0 on the bottom side), 35 nets.

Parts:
C1, C2: 1uF; C_0805_2012Metric_Pad1.18x1.45mm_HandSolder
C3: 0.1u; C_0603_1608Metric_Pad1.08x0.95mm_HandSolder
C4: 1u; C_0603_1608Metric_Pad1.08x0.95mm_HandSolder
C5: 220n; C_0603_1608Metric_Pad1.08x0.95mm_HandSolder
C6: 10n; C_0603_1608Metric_Pad1.08x0.95mm_HandSolder
C7: 10u; C_0805_2012Metric_Pad1.18x1.45mm_HandSolder
C8, C12: 2.2u; C_0805_2012Metric_Pad1.18x1.45mm_HandSolder
C9, C13: 100n; C_0603_1608Metric_Pad1.08x0.95mm_HandSolder
C10, C11, C14, C15: 47u; C_1210_3225Metric_Pad1.33x2.70mm_HandSolder
D1: 24VExt_LED; LED_0603_1608Metric_Pad1.05x0.95mm_HandSolder
D2: 24VLED_PP; LED_0603_1608Metric_Pad1.05x0.95mm_HandSolder
D3: 24VLED_12Buck; LED_0603_1608Metric_Pad1.05x0.95mm_HandSolder
D4: 24VLED_5Buck; LED_0603_1608Metric_Pad1.05x0.95mm_HandSolder
D5: 12VLED; LED_0603_1608Metric_Pad1.05x0.95mm_HandSolder
D6: 5VLED; LED_0603_1608Metric_Pad1.05x0.95mm_HandSolder
D7: 5VLED_LDO; LED_0603_1608Metric_Pad1.05x0.95mm_HandSolder
D8: 3v3LED_LDO; LED_0603_1608Metric_Pad1.05x0.95mm_HandSolder
D9: SBA130CH-AU_R1_000A1; D_SOD-323_HandSoldering
D10: SMBJ30CD; DIONM5436X244N
D11: SMAF4758A; SODFL5026X125N
F1: 5A; Fuse-3557-2
H1, H2, H3, H4: MountingHole_Pad_MP; MountingHole_3mm_Pad_TopBottom
IC1: LM74502DDFR
J1: 24V Test; 5754
J2: +24V_Ext; 5754
J3: 12V Test; 5754
J4: 5V Test; 5754
J5: 3V Test; 5754
J6: +V_in_24V; 5754
J7: GND; 5754
J8: +Vin_5V; 5754
JP1: 24V Load; PinHeader_1x02_P2.54mm_Vertical
JP2, JP7, JP8, JP9, JP10: 12V Load; PinHeader_1x02_P2.54mm_Vertical
JP3: 5V Load; PinHeader_1x02_P2.54mm_Vertical
JP4: 3V3 Load; PinHeader_1x02_P2.54mm_Vertical
JP5: PP-12V Buck; PinHeader_1x02_P2.54mm_Vertical
JP6: PP-5V Buck; PinHeader_1x02_P2.54mm_Vertical
JP11: 5V Buck-LDO; PinHeader_1x02_P2.54mm_Vertical
L1: 15u; L_TDK_VLP8040
L2: 10u; L_TDK_VLP8040
Q1, Q2: PSMN012-100YS
R1, R2, R3, R4: 22k; R_0603_1608Metric_Pad0.98x0.95mm_HandSolder
R5, R9, R13, R14: 10k; R_0603_1608Metric_Pad0.98x0.95mm_HandSolder
R6, R7: 2.2k; R_0603_1608Metric_Pad0.98x0.95mm_HandSolder
R8: 1k; R_0603_1608Metric_Pad0.98x0.95mm_HandSolder
R10: 33; R_0603_1608Metric_Pad0.98x0.95mm_HandSolder
R11: 221k; R_0603_1608Metric_Pad0.98x0.95mm_HandSolder
R12: 137k; R_0603_1608Metric_Pad0.98x0.95mm_HandSolder
R15: 143k; R_0603_1608Metric_Pad0.98x0.95mm_HandSolder
R16, R18: 10.2k; R_0603_1608Metric_Pad0.98x0.95mm_HandSolder
R17: 53.6k; R_0603_1608Metric_Pad0.98x0.95mm_HandSolder
TP1: 24V_Ext; TestPoint_THTPad_D3.0mm_Drill1.5mm
TP2, TP3, TP4: 24V_OUT; TestPoint_THTPad_D3.0mm_Drill1.5mm
TP5: 12V_Out; TestPoint_THTPad_D3.0mm_Drill1.5mm
TP6, TP7, TP8, TP9: GND; TestPoint_THTPad_D3.0mm_Drill1.5mm
TP10, TP19, TP20, TP21, TP22: +V_out_5V; TestPoint_THTPad_D3.0mm_Drill1.5mm
TP11: Vin_5V; TestPoint_THTPad_D3.0mm_Drill1.5mm
TP12: V_in_24V; TestPoint_THTPad_D3.0mm_Drill1.5mm
TP13, TP16: CB; TestPoint_THTPad_D3.0mm_Drill1.5mm
TP14, TP17: FB; TestPoint_THTPad_D3.0mm_Drill1.5mm
TP15, TP18: SW; TestPoint_THTPad_D3.0mm_Drill1.5mm
TP_3.3V1: 3.3V; TestPoint_THTPad_D3.0mm_Drill1.5mm
U1: MCP1826S_LDO; SOT-223-3_TabPin2
U2, U3: LMR51635XDDCR; DDC0006A-MFG

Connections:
/5VBuck/CB: C13.1, TP16.1, U3.6 (CB)
/5VBuck/FB: R17.2, R18.1, TP17.1, U3.1 (FB)
/5VBuck/SW: C13.2, L2.1, TP18.1, U3.5 (SW)
/12VBuck/CB: C9.1, TP13.1, U2.6 (CB)
/12VBuck/FB: R15.2, R16.1, TP14.1, U2.1 (FB)
/12VBuck/SW: C9.2, L1.1, TP15.1, U2.5 (SW)
/+24V_Ext: C3.1, D10.1 (K), F1.2, JP7.2 (B), Q1.5 (D), R1.1, R9.2, R11.1, R12.2, TP1.1
/+24V_Ext_In: F1.1, J2.1
/+V_in_24V: C8.1, C12.1, J6.1, JP5.2 (B), JP6.2 (B), R3.1, R4.1, TP12.1, U2.2 (EN), U2.3 (VIN), U3.2 (EN), U3.3 (VIN)
/+V_out_5V_Buck: C14.1, C15.1, JP11.1 (A), L2.2, R6.1, R17.1, TP10.1
/+Vin_5V: D9.2 (A), J8.1, JP3.2 (B), JP10.2 (B), JP11.2 (B), R7.1, TP11.1
/+Vout_3V3: C2.2, JP4.2 (B), JP8.2 (B), R8.1, TP_3.3V1.1, U1.3 (VO)
/PowerProtection/gate: C6.1, Q1.4 (G), Q2.4 (G), R10.1, TP2.1
/PowerProtection/source: IC1.8 (SRC), Q1.1 (S), Q1.2 (S), Q1.3 (S), Q2.1 (S), Q2.2 (S), Q2.3 (S), TP3.1
/V_out_12V: C10.1, C11.1, JP2.2 (B), JP9.2 (B), L1.2, R5.1, R15.1, TP5.1
/Vout_24V: C7.1, JP1.2 (B), JP5.1 (A), JP6.1 (A), Q2.5 (D), R2.1, TP4.1
GND: C1.1, C2.1, C3.2, C4.1, C6.2, C7.2, C8.2, C10.2, C11.2, C12.2, C14.2, C15.2, D1.1 (K), D2.1 (K), D3.1 (K), D4.1 (K), D5.1 (K), D6.1 (K), D7.1 (K), D8.1 (K), D10.2 (A), D11.2 (A), IC1.2 (GND), J7.1, JP7.1 (A), JP8.1 (A), JP9.1 (A), JP10.1 (A), R13.2, R14.2, R16.2, R18.2, TP6.1, TP7.1, TP8.1, TP9.1, U1.2 (GND), U2.4 (GND), U3.4 (GND)
unnamed: D1.2 (A), R1.2
unnamed: D2.2 (A), R2.2
unnamed: D3.2 (A), R3.2
unnamed: D4.2 (A), R4.2
unnamed: D5.2 (A), R5.2
unnamed: D6.2 (A), R6.2
unnamed: D7.2 (A), R7.2
unnamed: D8.2 (A), R8.2
unnamed: C1.2, D9.1 (K), U1.1 (VI)
unnamed: C4.2, C5.1, D11.1 (K), IC1.5 (VS), R9.1, TP19.1
unnamed: IC1.1 (EN/UVLO), R12.1, R14.1, TP22.1
unnamed: IC1.6 (GATE), R10.2
unnamed: IC1.7 (OV), R11.2, R13.1, TP21.1
unnamed: C5.2, IC1.4 (VCAP), TP20.1
unnamed: J1.1, JP1.1 (A)
unnamed: J3.1, JP2.1 (A)
unnamed: J4.1, JP3.1 (A)
unnamed: J5.1, JP4.1 (A)
